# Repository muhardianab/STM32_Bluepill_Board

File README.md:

# STM32_Bluepill_Board
ReDesign STM32 Bluepill Board

You can find the 3D file preview on [Grabcad](https://grabcad.com/library/stm32_bluepill-1)

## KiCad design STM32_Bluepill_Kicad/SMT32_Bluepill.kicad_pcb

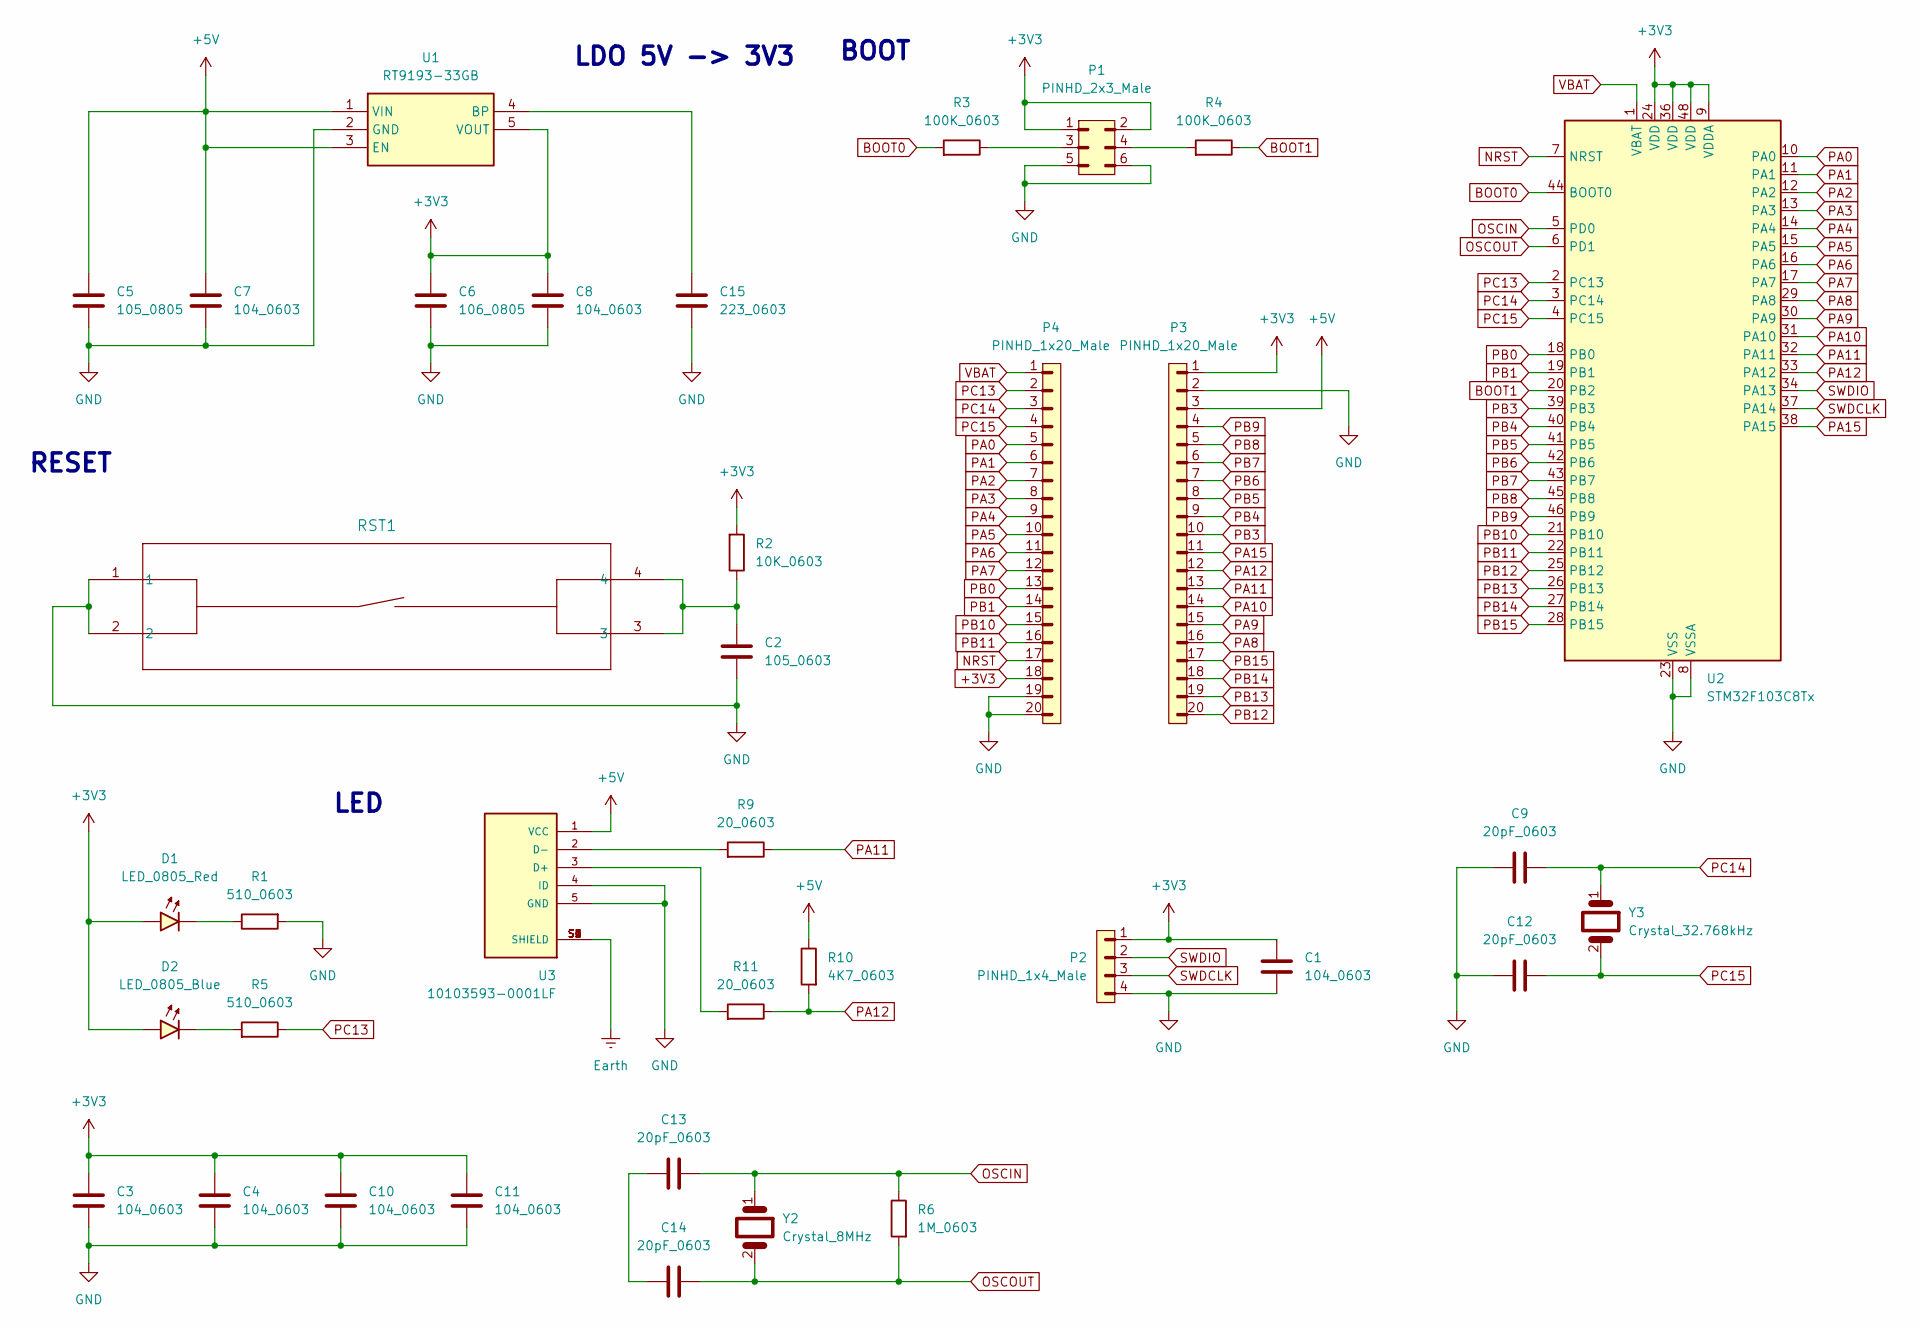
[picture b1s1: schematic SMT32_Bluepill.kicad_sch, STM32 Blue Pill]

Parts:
C1, C3, C4, C7, C8, C10, C11: 104_0603; C_0603_1608Metric
C2: 105_0603; C_0603_1608Metric
C5: 105_0805; C_0805_2012Metric
C6: 106_0805; C_0805_2012Metric
C9, C12, C13, C14: 20pF_0603; C_0603_1608Metric
C15: 223_0603; C_0603_1608Metric
D1: LED_0805_Red; LED_0805_2012Metric
D2: LED_0805_Blue; LED_0805_2012Metric
P1: PINHD_2x3_Male; PinHeader_2x03_P2.54mm_Vertical
P2: PINHD_1x4_Male; PinHeader_1x04_P2.54mm_Vertical
P3, P4: PINHD_1x20_Male; PinHeader_1x20_P2.54mm_Vertical
R1, R5: 510_0603; R_0603_1608Metric
R2: 10K_0603; R_0603_1608Metric
R3, R4: 100K_0603; R_0603_1608Metric
R6: 1M_0603; R_0603_1608Metric
R9, R11: 20_0603; R_0603_1608Metric
R10: 4K7_0603; R_0603_1608Metric
RST1: PTS526 SM15 SMTR2 LFS; SON4_PTS526 SM15 SMTR2 LFS_CNK-M
U1: RT9193-33GB; SOT94P279X130-5N; Mouser Part Number 835-RT9193-33GB
U2: STM32F103C8Tx; LQFP-48_7x7mm_P0.5mm
U3: 10103593-0001LF; AMPHENOL_10103593-0001LF; PARTREV A
Y2: Crystal_8MHz; Crystal_HC49-4H_Vertical
Y3: Crystal_32.768kHz; Crystal_AT310_D3.0mm_L10.0mm_Horizontal

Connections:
+3V3: C1.1, C3.1, C4.1, C6.1, C8.1, C10.1, C11.1, D1.2 (A), D2.2 (A), P1.1, P1.2, P2.1, P3.1, P4.18, R2.1, U1.5 (VOUT), U2.9 (VDDA), U2.24 (VDD), U2.36 (VDD), U2.48 (VDD)
+5V: C5.1, C7.1, P3.3, R10.2, U1.1 (VIN), U1.3 (EN), U3.1 (VCC)
BOOT0: R3.1, U2.44 (BOOT0)
BOOT1: R4.2, U2.20 (PB2)
Earth: U3.S1 (SHIELD), U3.S2 (SHIELD), U3.S3 (SHIELD), U3.S4 (SHIELD), U3.S5 (SHIELD), U3.S6 (SHIELD)
GND: C1.2, C2.2, C3.2, C4.2, C5.2, C6.2, C7.2, C8.2, C9.1, C10.2, C11.2, C12.1, C15.2, P1.5, P1.6, P2.4, P3.2, P4.19, P4.20, R1.1, RST1.1, RST1.2, U1.2 (GND), U2.8 (VSSA), U2.23 (VSS), U2.35 (VSS), U2.47 (VSS), U3.4 (ID), U3.5 (GND)
NRST: P4.17, U2.7 (NRST)
unnamed: C2.1, R2.2, RST1.3, RST1.4
unnamed: C13.1, C14.1
unnamed: D1.1 (K), R1.2
unnamed: D2.1 (K), R5.1
unnamed: P1.3, R3.2
unnamed: P1.4, R4.1
unnamed: C15.1, U1.4 (BP)
unnamed: R11.1, U3.3 (D+)
unnamed: R9.1, U3.2 (D-)
OSCIN: C13.2, R6.2, U2.5 (PD0), Y2.1
OSCOUT: C14.2, R6.1, U2.6 (PD1), Y2.2
PA0: P4.5, U2.10 (PA0)
PA1: P4.6, U2.11 (PA1)
PA2: P4.7, U2.12 (PA2)
PA3: P4.8, U2.13 (PA3)
PA4: P4.9, U2.14 (PA4)
PA5: P4.10, U2.15 (PA5)
PA6: P4.11, U2.16 (PA6)
PA7: P4.12, U2.17 (PA7)
PA8: P3.16, U2.29 (PA8)
PA9: P3.15, U2.30 (PA9)
PA10: P3.14, U2.31 (PA10)
PA11: P3.13, R9.2, U2.32 (PA11)
PA12: P3.12, R10.1, R11.2, U2.33 (PA12)
PA15: P3.11, U2.38 (PA15)
PB0: P4.13, U2.18 (PB0)
PB1: P4.14, U2.19 (PB1)
PB3: P3.10, U2.39 (PB3)
PB4: P3.9, U2.40 (PB4)
PB5: P3.8, U2.41 (PB5)
PB6: P3.7, U2.42 (PB6)
PB7: P3.6, U2.43 (PB7)
PB8: P3.5, U2.45 (PB8)
PB9: P3.4, U2.46 (PB9)
PB10: P4.15, U2.21 (PB10)
PB11: P4.16, U2.22 (PB11)
PB12: P3.20, U2.25 (PB12)
PB13: P3.19, U2.26 (PB13)
PB14: P3.18, U2.27 (PB14)
PB15: P3.17, U2.28 (PB15)
PC13: P4.2, R5.2, U2.2 (PC13)
PC14: C9.2, P4.3, U2.3 (PC14), Y3.1
PC15: C12.2, P4.4, U2.4 (PC15), Y3.2
SWDCLK: P2.3, U2.37 (PA14)
SWDIO: P2.2, U2.34 (PA13)
VBAT: P4.1, U2.1 (VBAT)

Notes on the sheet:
LED
LDO 5V -> 3V3
BOOT
RESET

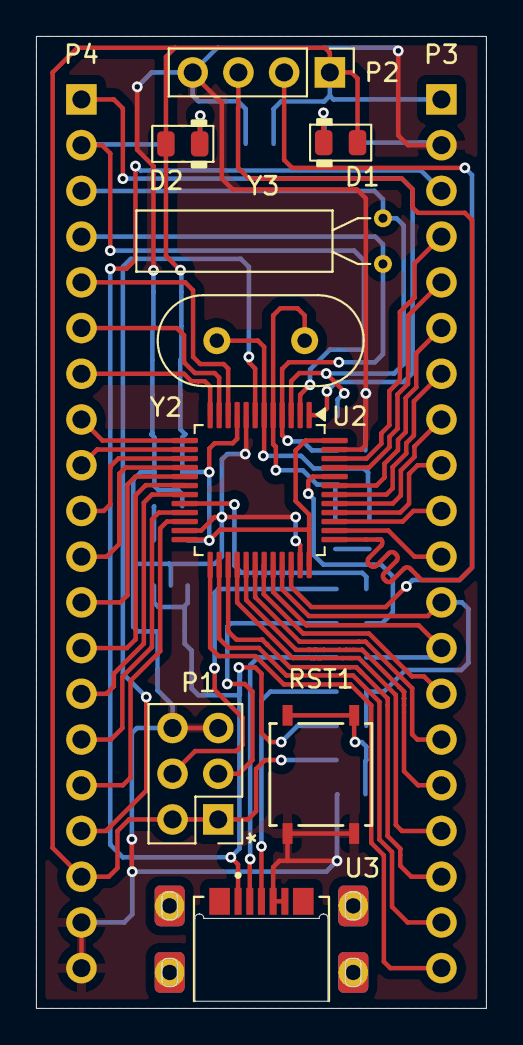
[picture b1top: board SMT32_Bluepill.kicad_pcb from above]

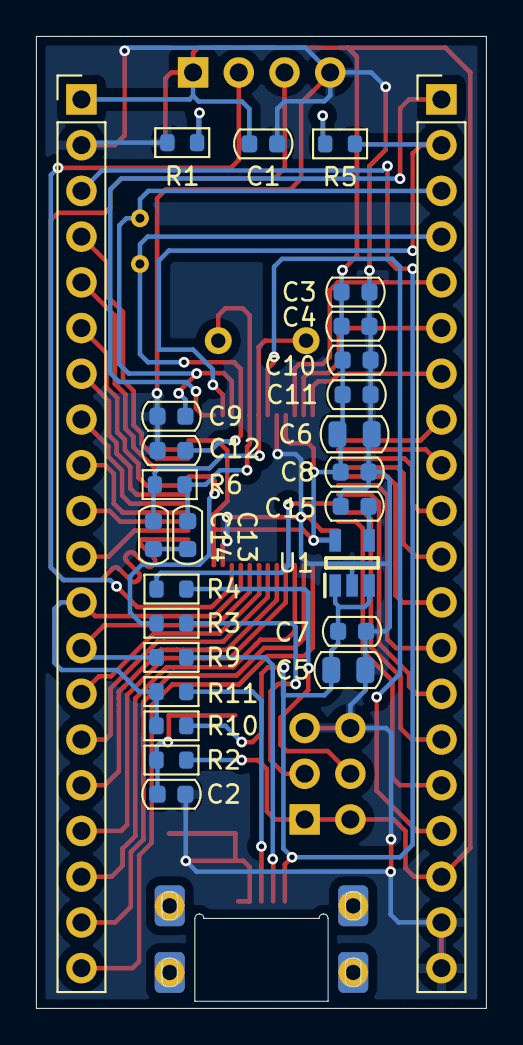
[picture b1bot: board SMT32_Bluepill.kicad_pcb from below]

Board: 2 copper layers, 25.0 x 54.0 mm, 36 parts (27 on the bottom side), 53 nets.

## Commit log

2025-02-25 First Upload
2025-02-25 Move folder
2025-02-25 Schematic done, PCB 50%
    Component placements still undone
2025-02-26 PCB 70%
    This version haven't been to redesign
2025-02-27 PCB 80%
    There are some traces that need to be retraced
2025-02-28 Final R0
    Done R0
2025-03-05 update
    only update the time modification, no additional thing
2025-09-29 Update board and preview
    Update the 3D components of the library and preview of the board
2025-09-29 Update the 3D and preview
2025-09-29 Rename files
2026-03-23 Daily update
